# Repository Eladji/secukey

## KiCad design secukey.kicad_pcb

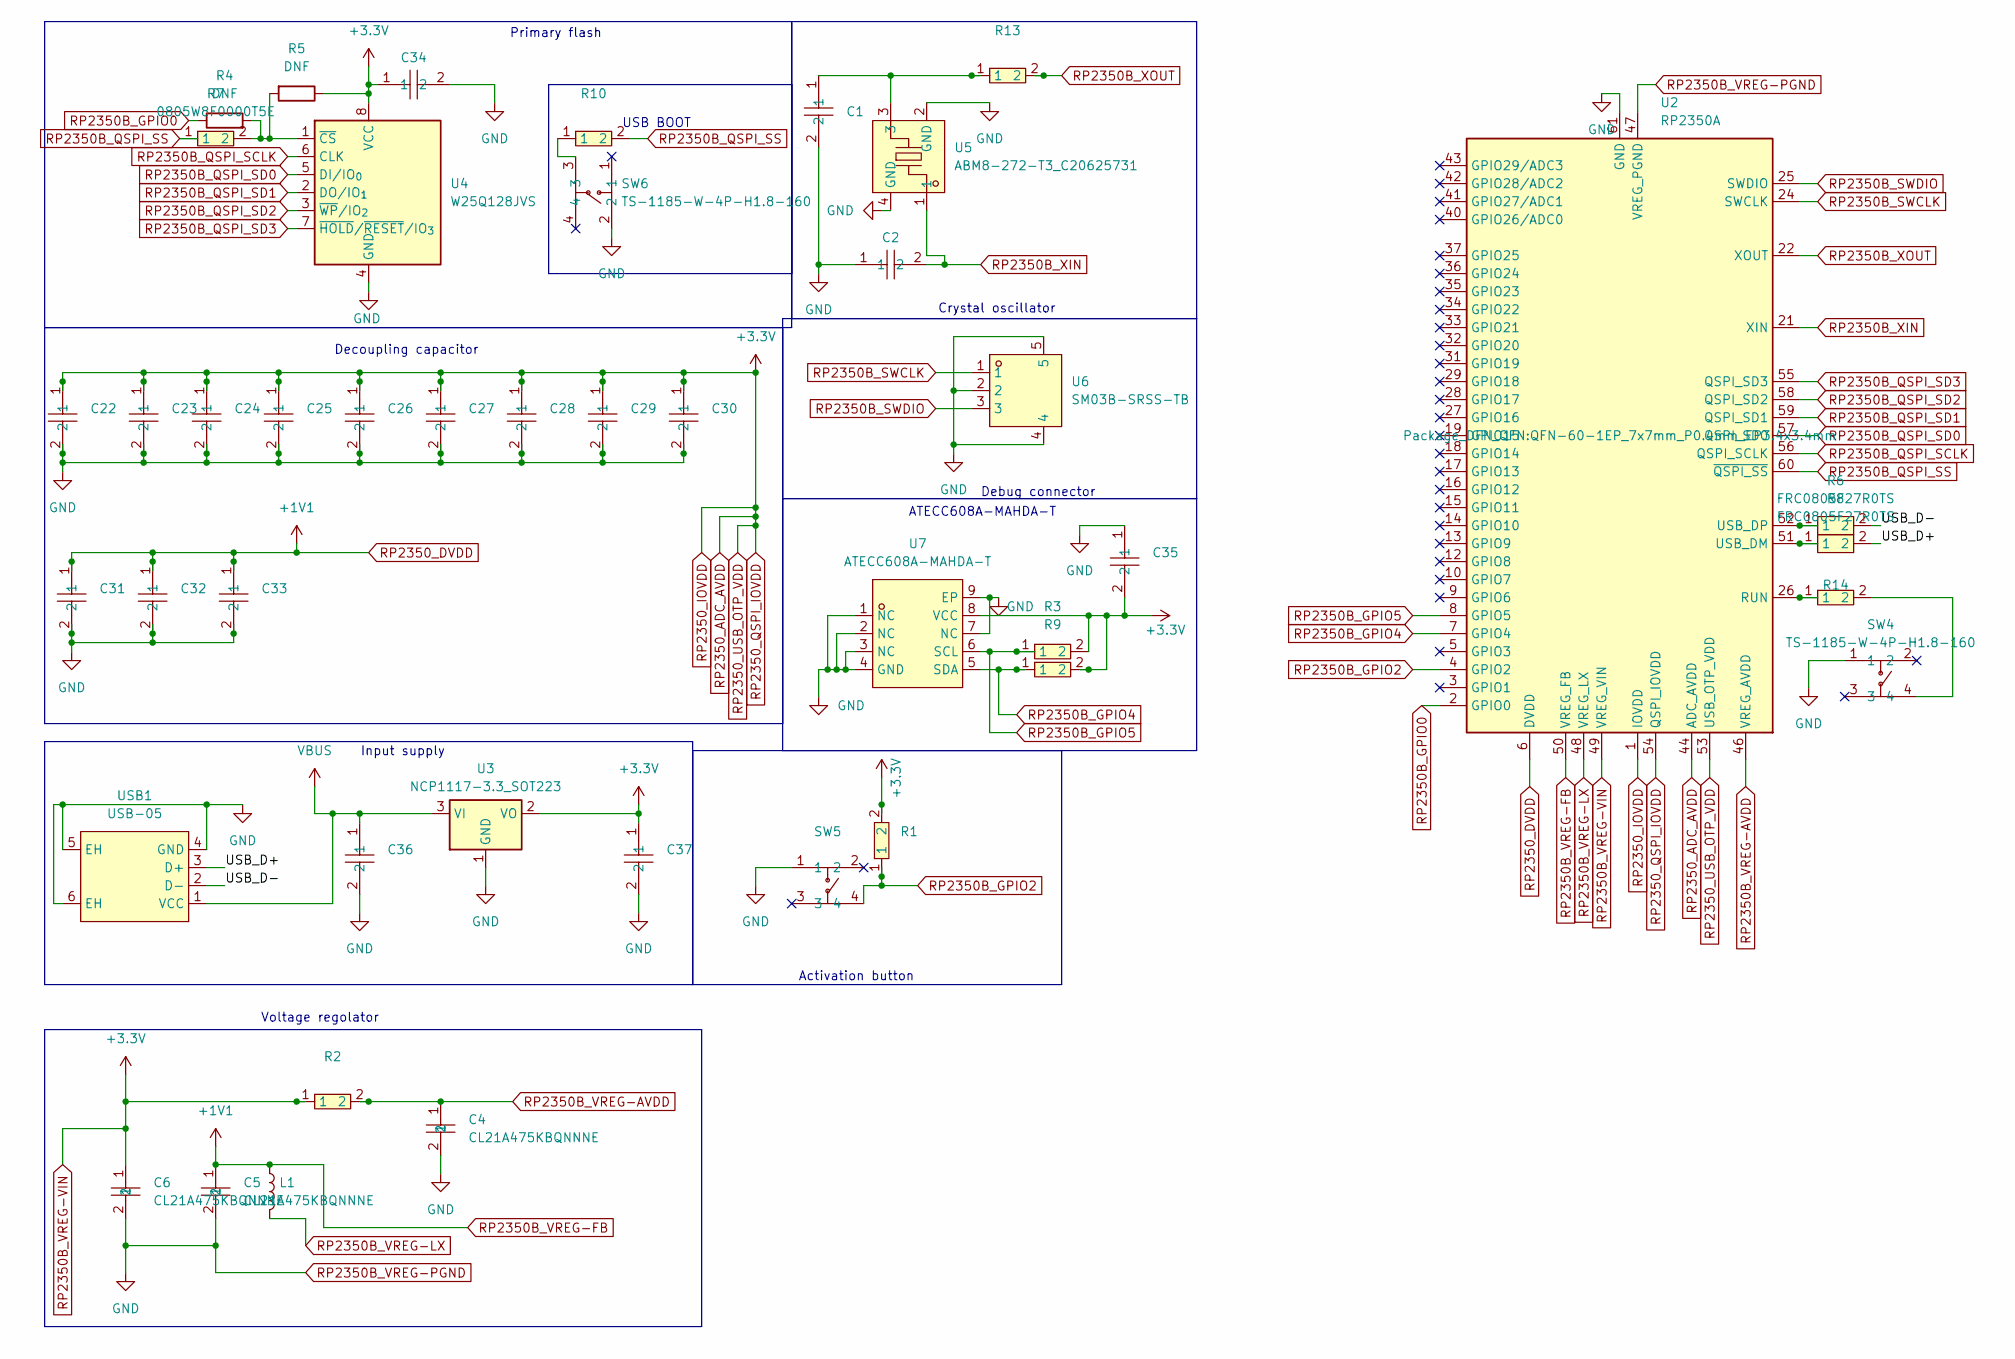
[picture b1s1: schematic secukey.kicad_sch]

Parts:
C1, C2: FCC0805N150J500BT; C0805; MPN FCC0805N150J500BT; LCSC Part C7467172
C4, C5, C6: CL21A475KBQNNNE; C0805; MPN CL21A475KBQNNNE; LCSC Part C98192
C22, C23, C24, C25, C26, C27, C28, C29, C30, C31, C32, C33, C34, C35, C36, C37: CC0402KRX7R5BB104; C0402; MPN CC0402KRX7R5BB104; LCSC Part C541406
L1: 3.3u; IND-SMD_L2.0-W1.6_AOTA-B201610S3R3-101-T
R1: RC0805JR-0710KL; R0805; MPN RC0805JR-0710KL; LCSC Part C100047
R2: 0805W8J0330T5E; R0805; MPN 0805W8J0330T5E; LCSC Part C25307
R3, R9: 0805W8F4701T5E; R0805; MPN 0805W8F4701T5E; LCSC Part C17673
R4, R5: DNF; R_0402_1005Metric
R6, R8: FRC0805F27R0TS; R0805; MPN FRC0805F27R0TS; LCSC Part C2933393
R7: 0805W8F0000T5E; R0805; MPN 0805W8F0000T5E; LCSC Part C17477
R10, R13, R14: RC0805JR-071KL; R0805; MPN RC0805JR-071KL; LCSC Part C100046
SW4, SW5, SW6: TS-1185-W-4P-H1.8-160; SW-SMD_4P-L3.5-W3.0-P1.50-LS4.7; MPN TS-1185-W-4P-H1.8-160; LCSC Part C51927445
U2: RP2350A; QFN-60-1EP_7x7mm_P0.4mm_EP3.4x3.4mm
U3: NCP1117-3.3_SOT223; SOT-223-3_TabPin2
U4: W25Q128JVS; SOIC-8_5.3x5.3mm_P1.27mm
U5: ABM8-272-T3_C20625731; CRYSTAL-SMD_4P-L3.2-W2.5-BL; MPN ABM8-272-T3; LCSC Part C20625731
U6: SM03B-SRSS-TB; CONN-SMD_SM03B-SRSS-TB-LF-SN-P; MPN SM03B-SRSS-TB(LF)(SN); LCSC Part C160403
U7: ATECC608A-MAHDA-T; UDFN-8_L3.0-W2.0-P0.50-BL-EP-1; MPN ATECC608A-MAHDA-T; LCSC Part C616909
USB1: USB-05; USB_A_CNCTech_1001-011-01101_Horizontal; MPN USB-05; LCSC Part C112454

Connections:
/USB_D+: R8.2, USB1.3 (D+)
/USB_D-: R6.2, USB1.2 (D-)
unnamed: C1.1, R13.1, U5.3
unnamed: R10.1, SW6.3
unnamed: R14.2, SW4.4
unnamed: R14.1, U2.26 (RUN)
unnamed: R8.1, U2.51 (USB_DM)
unnamed: R6.1, U2.52 (USB_DP)
unnamed: R4.2, R5.2, R7.2, U4.1 (~CS)
RP2350B_GPIO0: R4.1, U2.2 (GPIO0)
RP2350B_GPIO2: R1.1, SW5.4, U2.4 (GPIO2)
RP2350B_GPIO4: R9.1, U2.7 (GPIO4), U7.5 (SDA)
RP2350B_GPIO5: R3.1, U2.8 (GPIO5), U7.6 (SCL)
RP2350B_QSPI_SCLK: U2.56 (QSPI_SCLK), U4.6 (CLK)
RP2350B_QSPI_SD0: U2.57 (QSPI_SD0), U4.5 (DI/IO_{0})
RP2350B_QSPI_SD1: U2.59 (QSPI_SD1), U4.2 (DO/IO_{1})
RP2350B_QSPI_SD2: U2.58 (QSPI_SD2), U4.3 (~WP/IO_{2})
RP2350B_QSPI_SD3: U2.55 (QSPI_SD3), U4.7 (~HOLD/~RESET/IO_{3})
RP2350B_QSPI_SS: R7.1, R10.2, U2.60 (~QSPI_SS)
RP2350B_SWCLK: U2.24 (SWCLK), U6.1
RP2350B_SWDIO: U2.25 (SWDIO), U6.3
RP2350B_VREG-AVDD: C4.1, R2.2, U2.46 (VREG_AVDD)
RP2350B_VREG-FB: C5.1, C31.1, C32.1, C33.1, L1.1, U2.6 (DVDD), U2.23 (DVDD), U2.39 (DVDD), U2.50 (VREG_FB)
RP2350B_VREG-LX: L1.2, U2.48 (VREG_LX)
RP2350B_VREG-PGND: C1.2, C2.1, C4.2, C5.2, C6.2, C22.2, C23.2, C24.2, C25.2, C26.2, C27.2, C28.2, C29.2, C30.2, C31.2, C32.2, C33.2, C34.2, C35.1, C36.2, C37.2, SW4.1, SW5.1, SW6.2, U2.47 (VREG_PGND), U2.61 (GND), U3.1 (GND), U4.4 (GND), U5.2 (GND), U5.4 (GND), U6.2, U6.4, U6.5, U7.1 (NC), U7.2 (NC), U7.3 (NC), U7.4 (GND), U7.7 (NC), U7.9 (EP), USB1.4 (GND), USB1.5 (EH), USB1.6 (EH)
RP2350B_VREG-VIN: C6.1, C22.1, C23.1, C24.1, C25.1, C26.1, C27.1, C28.1, C29.1, C30.1, C34.1, C35.2, C37.1, R1.2, R2.1, R3.2, R5.1, R9.2, U2.1 (IOVDD), U2.11 (IOVDD), U2.20 (IOVDD), U2.30 (IOVDD), U2.38 (IOVDD), U2.44 (ADC_AVDD), U2.45 (IOVDD), U2.49 (VREG_VIN), U2.53 (USB_OTP_VDD), U2.54 (QSPI_IOVDD), U3.2 (VO), U4.8 (VCC), U7.8 (VCC)
RP2350B_XIN: C2.2, U2.21 (XIN), U5.1
RP2350B_XOUT: R13.2, U2.22 (XOUT)
VBUS: C36.1, U3.3 (VI), USB1.1 (VCC)

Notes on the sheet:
Primary flash
ATECC608A-MAHDA-T
Voltage regolator
Crystal oscillator
Decoupling capacitor
Input supply
USB BOOT
Activation button
Debug connector

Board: 2 copper layers, 44 parts (0 on the bottom side), 29 nets, no tracks yet.

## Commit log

2026-05-03 init commit
2026-05-04 updated capacitor placement
2026-05-04 rearrange the placement for power route
2026-05-04 added missing library
2026-05-05 adding ref
2026-05-06 adding made placement
